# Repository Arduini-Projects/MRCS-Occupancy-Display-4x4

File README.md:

# MRCS-Occupancy-Display

## License: Creative Commons Attribution-NonCommercial-ShareAlike

Allison wanted to take an input from the open drain/collector of a cpOD/DCC-OD and drive a bi-color LED to show occupancy status. The plan is a hex inverter (7404/7407) to provide the other status
so the occupied indication is driven from the cpOD/DCC-OD and "not occupied"indication comes from the inverter. Limiting resistors are provided.

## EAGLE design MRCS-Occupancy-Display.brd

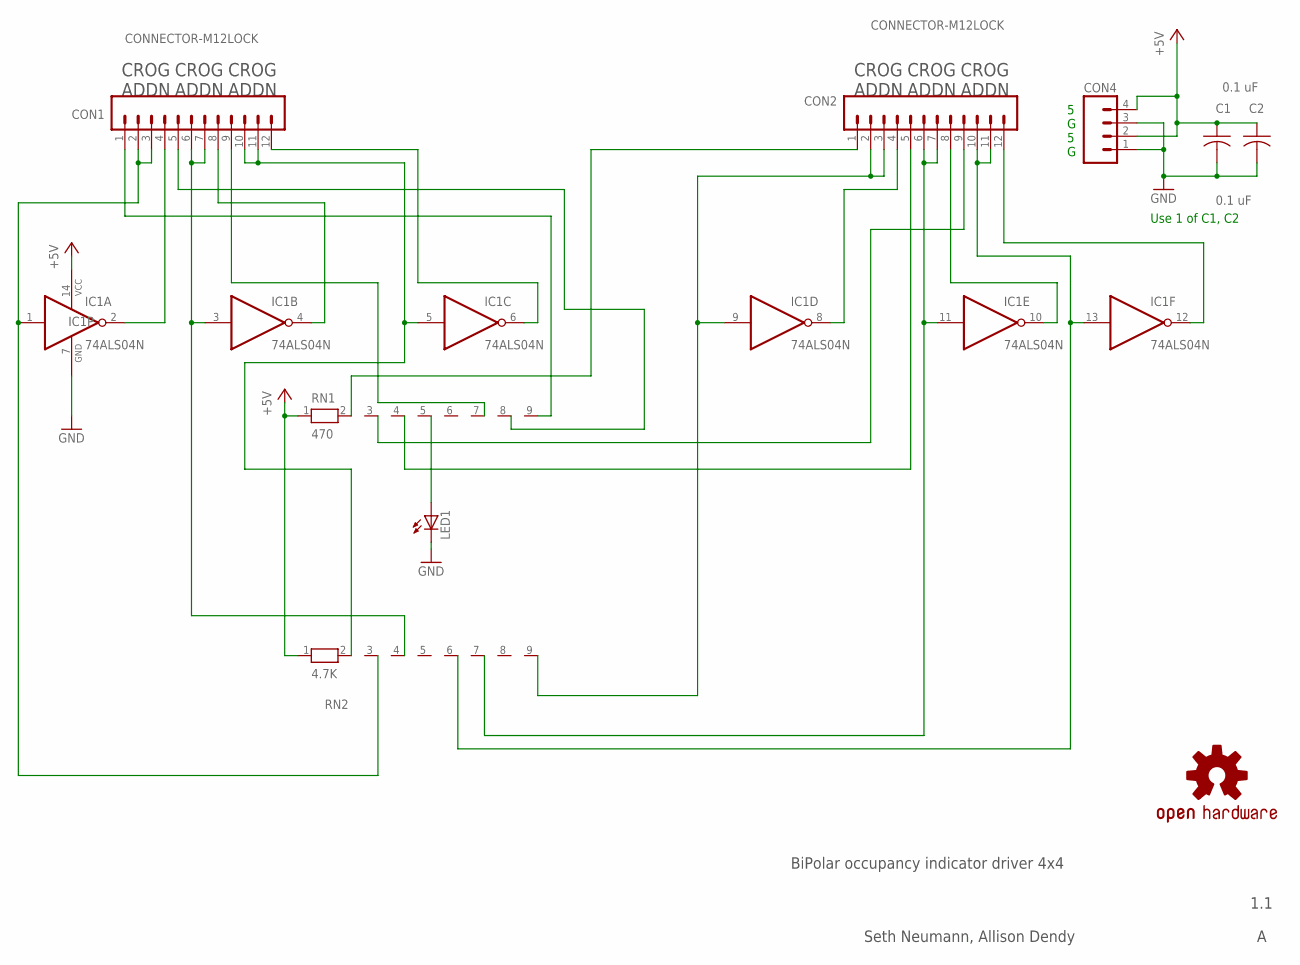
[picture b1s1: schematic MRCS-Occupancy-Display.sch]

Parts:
C1: 0.1 uF; C-PTH-0.100
C2: 0.1 uF; C050-024X044
CON1, CON2: CONNECTOR-M12LOCK; 1X12_LOCK
CON4: CONNECTOR-M04SCREW; SCREWTERMINAL-3.5MM-4
IC1: 74ALS04N; DIL14
LED1: LEDLED3MM; LED3MM
OSHW1: DOC-OSHW-LOGO-M; OSHW-LOGO-M
RN1: 470; RN-9
RN2: 4.7K; RN-9

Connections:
GND: C1.2, C2.2, CON4.1, CON4.3, IC1.7 (GND), LED1.K (C)
unnamed: CON1.10, CON1.11, IC1.5 (I), RN2.2
unnamed: CON1.1, RN1.9
unnamed: CON1.4, IC1.2 (O)
unnamed: CON1.6, CON1.7, IC1.3 (I), RN2.4
unnamed: CON1.12, IC1.6 (O)
unnamed: CON1.8, IC1.4 (O)
unnamed: CON1.5, RN1.8
unnamed: CON2.2, CON2.3, IC1.9 (I), RN2.9
unnamed: CON1.9, RN1.7
unnamed: CON2.8, IC1.10 (O)
unnamed: CON2.12, IC1.12 (O)
unnamed: CON2.4, IC1.8 (O)
unnamed: CON2.1, RN1.2
unnamed: CON2.5, RN1.4
unnamed: CON1.2, CON1.3, IC1.1 (I), RN2.3
unnamed: LED1.A, RN1.5
unnamed: CON2.6, CON2.7, IC1.11 (I), RN2.7
unnamed: CON2.9, RN1.3
unnamed: CON2.10, CON2.11, IC1.13 (I), RN2.6
VCC: C1.1, C2.1, CON4.2, CON4.4, IC1.14 (VCC), RN1.1, RN2.1

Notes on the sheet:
BiPolar occupancy indicator driver 4x4
1.1
Seth Neumann, Allison Dendy
CROG ADDN
5 G 5 G
Use 1 of C1, C2

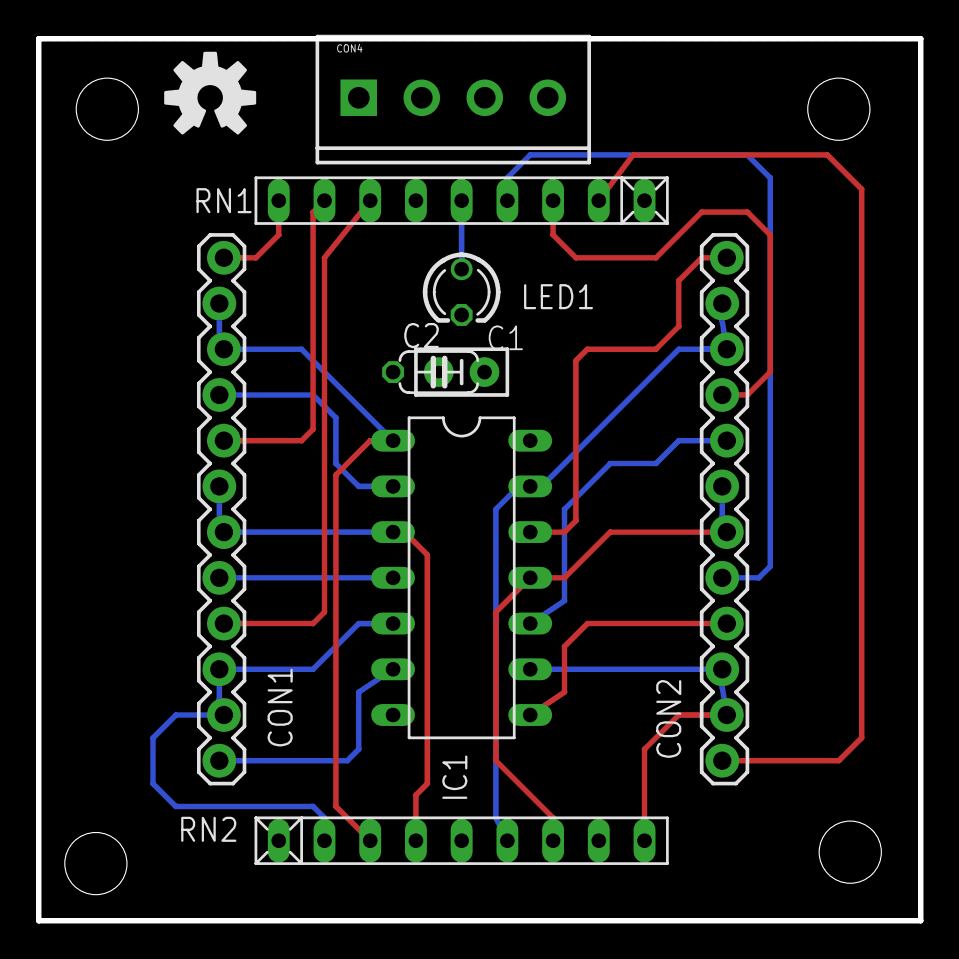
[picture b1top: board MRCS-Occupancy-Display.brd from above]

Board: 2 copper layers, 49.0 x 49.0 mm, 12 parts (0 on the bottom side), 21 nets.

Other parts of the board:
U$1: CA-PROP65WARNING
U$2: MRCSLOGOBTM

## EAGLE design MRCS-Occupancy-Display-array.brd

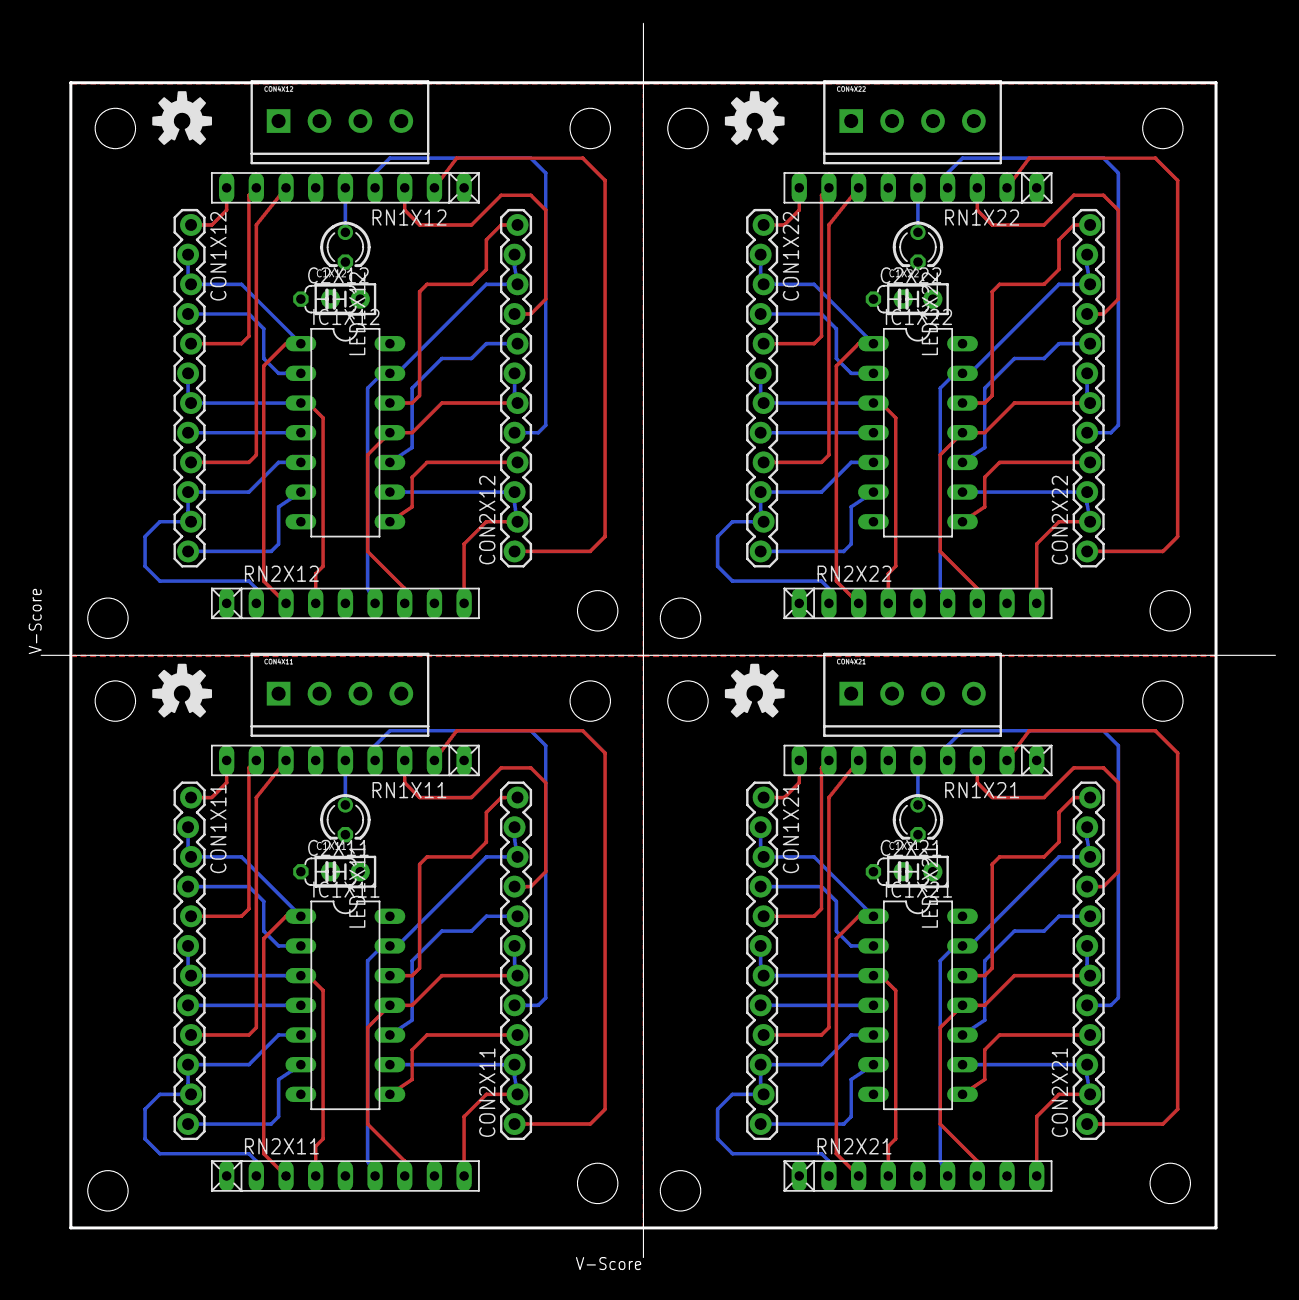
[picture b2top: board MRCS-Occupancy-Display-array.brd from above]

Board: 2 copper layers, 105.6 x 105.6 mm, 48 parts (0 on the bottom side), 84 nets.

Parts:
C1X11, C1X12, C1X21, C1X22: 0.1 uF; C-PTH-0.100
C2X11, C2X12, C2X21, C2X22: 0.1 uF; C050-024X044
CON1X11, CON1X12, CON1X21, CON1X22, CON2X11, CON2X12, CON2X21, CON2X22: CONNECTOR-M12LOCK; 1X12_LOCK
CON4X11, CON4X12, CON4X21, CON4X22: SCREWTERMINAL-3.5MM-4
IC1X11, IC1X12, IC1X21, IC1X22: 74ALS04N; DIL14
LED1X11, LED1X12, LED1X21, LED1X22: LED3MM
OSHW1X11, OSHW1X12, OSHW1X21, OSHW1X22: DOC-OSHW-LOGO-M; OSHW-LOGO-M
RN1X11, RN1X12, RN1X21, RN1X22: 470; RN-9
RN2X11, RN2X12, RN2X21, RN2X22: 4.7K; RN-9
U$1X11, U$1X12, U$1X21, U$1X22: CA-PROP65WARNING
U$2X11, U$2X12, U$2X21, U$2X22: MRCSLOGOBTM

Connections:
GNDX11: C1X11.2, C2X11.2, CON4X11.1, CON4X11.3, IC1X11.7, LED1X11.K
GNDX12: C1X12.2, C2X12.2, CON4X12.1, CON4X12.3, IC1X12.7, LED1X12.K
GNDX21: C1X21.2, C2X21.2, CON4X21.1, CON4X21.3, IC1X21.7, LED1X21.K
GNDX22: C1X22.2, C2X22.2, CON4X22.1, CON4X22.3, IC1X22.7, LED1X22.K
unnamed: CON1X11.10, CON1X11.11, IC1X11.5, RN2X11.2
unnamed: CON1X12.10, CON1X12.11, IC1X12.5, RN2X12.2
unnamed: CON1X21.10, CON1X21.11, IC1X21.5, RN2X21.2
unnamed: CON1X22.10, CON1X22.11, IC1X22.5, RN2X22.2
unnamed: CON1X11.1, RN1X11.9
unnamed: CON1X12.1, RN1X12.9
unnamed: CON1X21.1, RN1X21.9
unnamed: CON1X22.1, RN1X22.9
unnamed: CON1X11.4, IC1X11.2
unnamed: CON1X12.4, IC1X12.2
unnamed: CON1X21.4, IC1X21.2
unnamed: CON1X22.4, IC1X22.2
unnamed: CON1X11.6, CON1X11.7, IC1X11.3, RN2X11.4
unnamed: CON1X12.6, CON1X12.7, IC1X12.3, RN2X12.4
unnamed: CON1X21.6, CON1X21.7, IC1X21.3, RN2X21.4
unnamed: CON1X22.6, CON1X22.7, IC1X22.3, RN2X22.4
unnamed: CON1X11.12, IC1X11.6
unnamed: CON1X12.12, IC1X12.6
unnamed: CON1X21.12, IC1X21.6
unnamed: CON1X22.12, IC1X22.6
unnamed: CON1X11.8, IC1X11.4
unnamed: CON1X12.8, IC1X12.4
unnamed: CON1X21.8, IC1X21.4
unnamed: CON1X22.8, IC1X22.4
unnamed: CON1X11.5, RN1X11.8
unnamed: CON1X12.5, RN1X12.8
unnamed: CON1X21.5, RN1X21.8
unnamed: CON1X22.5, RN1X22.8
unnamed: CON2X11.2, CON2X11.3, IC1X11.9, RN2X11.9
unnamed: CON2X12.2, CON2X12.3, IC1X12.9, RN2X12.9
unnamed: CON2X21.2, CON2X21.3, IC1X21.9, RN2X21.9
unnamed: CON2X22.2, CON2X22.3, IC1X22.9, RN2X22.9
unnamed: CON1X11.9, RN1X11.7
unnamed: CON1X12.9, RN1X12.7
unnamed: CON1X21.9, RN1X21.7
unnamed: CON1X22.9, RN1X22.7
unnamed: CON2X11.8, IC1X11.10
unnamed: CON2X12.8, IC1X12.10
unnamed: CON2X21.8, IC1X21.10
unnamed: CON2X22.8, IC1X22.10
unnamed: CON2X11.12, IC1X11.12
unnamed: CON2X12.12, IC1X12.12
unnamed: CON2X21.12, IC1X21.12
unnamed: CON2X22.12, IC1X22.12
unnamed: CON2X11.4, IC1X11.8
unnamed: CON2X12.4, IC1X12.8
unnamed: CON2X21.4, IC1X21.8
unnamed: CON2X22.4, IC1X22.8
unnamed: CON2X11.1, RN1X11.2
unnamed: CON2X12.1, RN1X12.2
unnamed: CON2X21.1, RN1X21.2
unnamed: CON2X22.1, RN1X22.2
unnamed: CON2X11.5, RN1X11.4
unnamed: CON2X12.5, RN1X12.4
unnamed: CON2X21.5, RN1X21.4
unnamed: CON2X22.5, RN1X22.4
unnamed: CON1X11.2, CON1X11.3, IC1X11.1, RN2X11.3
unnamed: CON1X12.2, CON1X12.3, IC1X12.1, RN2X12.3
unnamed: CON1X21.2, CON1X21.3, IC1X21.1, RN2X21.3
unnamed: CON1X22.2, CON1X22.3, IC1X22.1, RN2X22.3
unnamed: LED1X11.A, RN1X11.5
unnamed: LED1X12.A, RN1X12.5
unnamed: LED1X21.A, RN1X21.5
unnamed: LED1X22.A, RN1X22.5
unnamed: CON2X11.6, CON2X11.7, IC1X11.11, RN2X11.7
unnamed: CON2X12.6, CON2X12.7, IC1X12.11, RN2X12.7
unnamed: CON2X21.6, CON2X21.7, IC1X21.11, RN2X21.7
unnamed: CON2X22.6, CON2X22.7, IC1X22.11, RN2X22.7
unnamed: CON2X11.9, RN1X11.3
unnamed: CON2X12.9, RN1X12.3
unnamed: CON2X21.9, RN1X21.3
unnamed: CON2X22.9, RN1X22.3
unnamed: CON2X11.10, CON2X11.11, IC1X11.13, RN2X11.6
unnamed: CON2X12.10, CON2X12.11, IC1X12.13, RN2X12.6
unnamed: CON2X21.10, CON2X21.11, IC1X21.13, RN2X21.6
unnamed: CON2X22.10, CON2X22.11, IC1X22.13, RN2X22.6
VCCX11: C1X11.1, C2X11.1, CON4X11.2, CON4X11.4, IC1X11.14, RN1X11.1, RN2X11.1
VCCX12: C1X12.1, C2X12.1, CON4X12.2, CON4X12.4, IC1X12.14, RN1X12.1, RN2X12.1
VCCX21: C1X21.1, C2X21.1, CON4X21.2, CON4X21.4, IC1X21.14, RN1X21.1, RN2X21.1
VCCX22: C1X22.1, C2X22.1, CON4X22.2, CON4X22.4, IC1X22.14, RN1X22.1, RN2X22.1

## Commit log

2023-09-19 intial commit
2023-09-19 early noodling on thru hole design
2023-09-20 first pass of V1.0
    basic 5x7 CM board per Allison
2023-09-21 modified the base design from 5x7 to 5x5 CM
    The intent is to make a smaller footprint for panelization. It's pretty tight and not much room for labels.
2023-11-29 cleanup prior to putting product up on website

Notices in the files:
parts and their libraries:
SPCoast: http://freedomdefined.org/OSHW Creative Commons - Attribution - ShareAlike 3.0
